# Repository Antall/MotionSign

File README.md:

View this project on [CADLAB.io](https://cadlab.io/node/895). 

# MotionSign
Controls sign activated by motion sensor.

# Setup

## Setting up Arduino and Compiling the Code (MAC)

1. Clone this repo to `~/Documents/Arduino` with `cd ~/Documents/Arduino && git clone git@github.com:bguest/MotionSign.git`
2. Change directory to MotionSign with `cd MotionSign`
3. Mod setup script `chmod +x setup.sh`
4. Run Setup `.\setup.sh` this will clone correct versions of `Adafruit_WS2801`
5. Download Arduino
6. Launch Arduino
7. Open MotionSign328
8. Set board to `Arduino HUZZAH ESP8266`
9. Set cpu frequency to `80MHz`
10. Set upload speed to `115200`
10. Verify and Upload Code

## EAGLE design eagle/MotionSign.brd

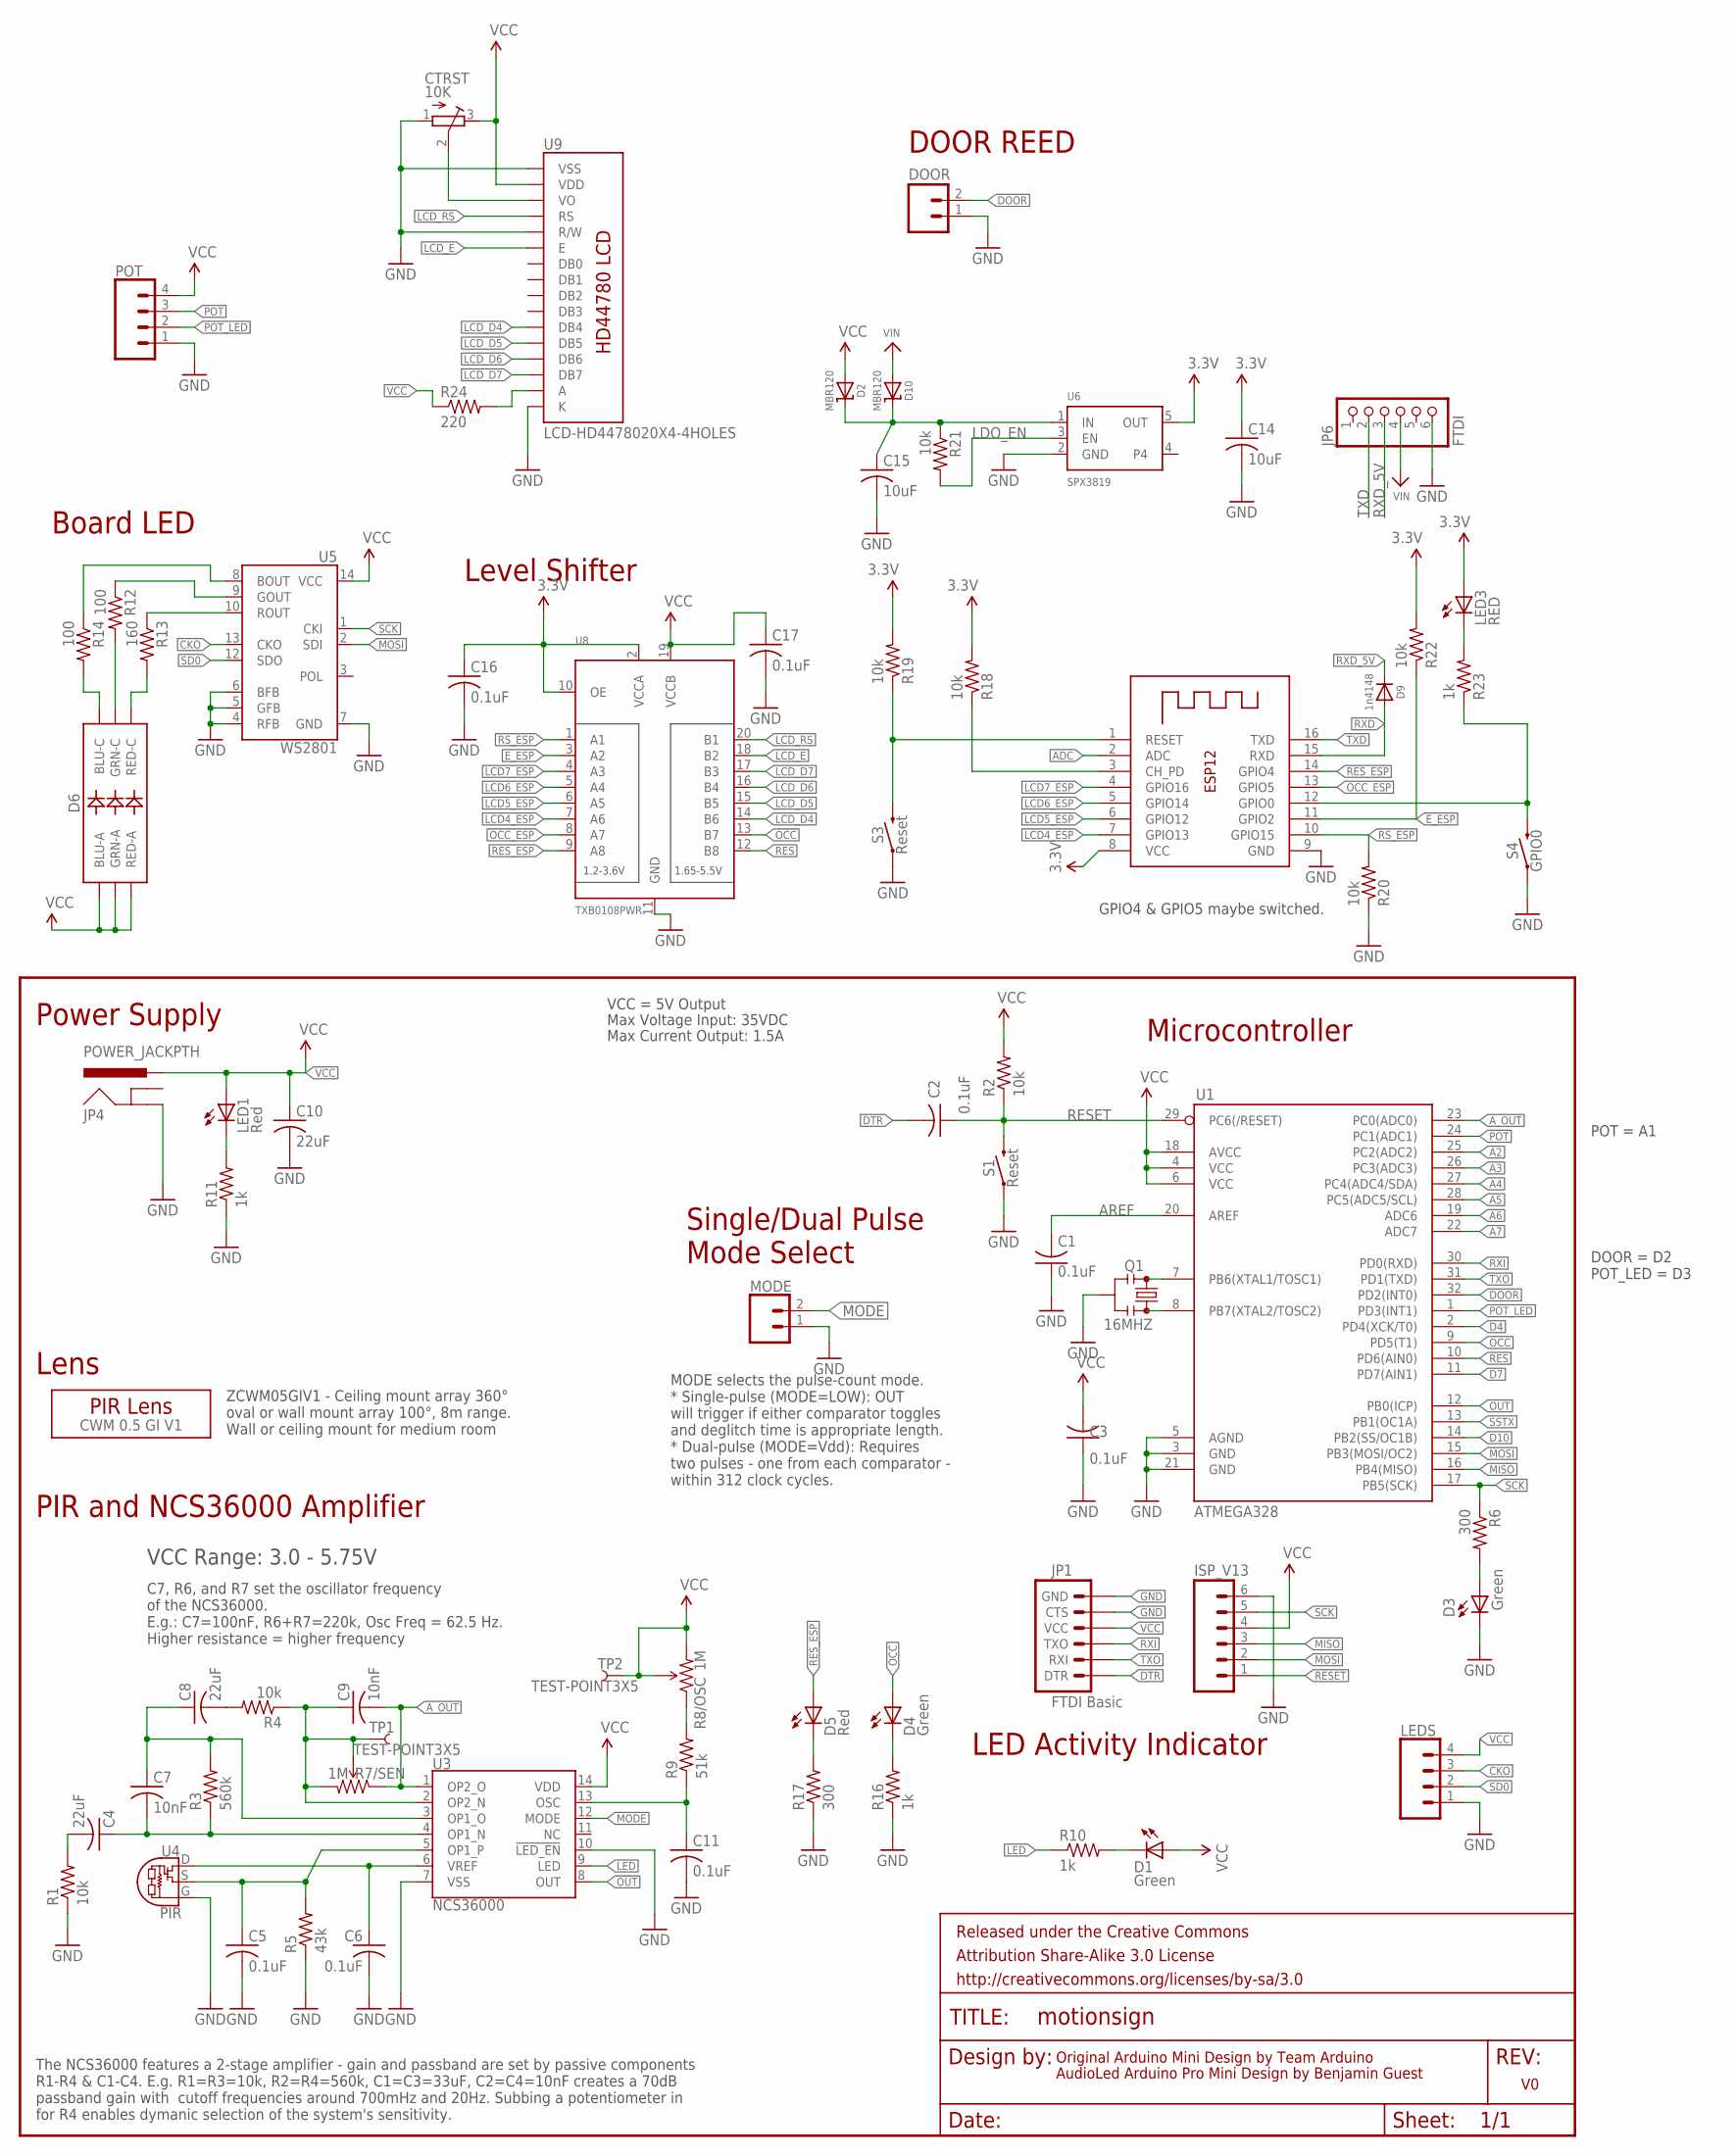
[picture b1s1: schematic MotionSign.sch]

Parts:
C1, C2, C3, C5, C6, C11, C16, C17: 0.1uF; C0805
C4, C8, C10: 22uF; C0805
C7, C9: 10nF; C0805
C14, C15: 10uF; C0805
CTRST: 10K; RTRIM3296W
D1, D3, D4: Green; CHIPLED_0805
D2, D10: MBR120; SOD-123
D5: Red; CHIPLED_0805
D6: LED-RGBNO_IC; LED-TRICOLOR-5050
D9: 1n4148; SOD-323
DOOR: CONN_02JST-PTH-2; JST-2-PTH
FRAME1: FRAME-LETTER; CREATIVE_COMMONS
ISP_V13: M06SIP; 1X06
JP1: FTDI Basic; 1X06
JP4: POWER_JACKPTH; POWER_JACK_PTH
JP6: FTDI; 1X06_ROUND_70
LED1: Red; CHIPLED_0805
LED3: RED; CHIP-LED0805
LEDS: CONN_04JST-PTH; JST-4-PTH
MODE: CONN_02; 1X02
POT: CONN_04JST-PTH; JST-4-PTH
Q1: 16MHZ; RESONATOR-SMD
R1, R2, R4, R18, R19, R20, R21, R22: 10k; M0805
R3: 560k; M0805
R5: 43k; M0805
R6, R17: 300; M0805
R7/SEN, R8/OSC: 1M; TRIMPOT-TC33X
R9: 51k; M0805
R10, R11, R16, R23: 1k; M0805
R12, R14: 100; M0805
R13: 160; M0805
R24: 220; 0204/7
S1, S3: Reset; TACTILE_SWITCH_SMD_5.2MM
S4: GPIO0; TACTILE_SWITCH_SMD_5.2MM
TP1, TP2: TEST-POINT3X5; PAD.03X.05
U1: ATMEGA328; TQFP32-08
U3: NCS36000; SO14
U4: PIR
U5: WS2801; SOP-14
U6: SPX3819; SOT23-5
U8: TXB0108PWR; TSSOP20
U9: LCD-HD4478020X4-4HOLES; LCD-20X4-1HOLE_NOSILK
U$1: CWM 0.5 GI V1; LENS-CWM-0.5-GI-V1
X2: ESP-12

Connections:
3.3V: C14.1, C16.1, LED3.A, R18.2, R19.2, R22.2, U6.5 (OUT), U8.2 (VCCA), U8.10 (OE), X2.8 (VCC)
A2: U1.25 (PC2(ADC2))
A3: U1.26 (PC3(ADC3))
A4: U1.27 (PC4(ADC4/SDA))
A5: U1.28 (PC5(ADC5/SCL))
A6: U1.19 (ADC6)
A7: U1.22 (ADC7)
ADC: X2.2 (ADC)
AREF: C1.2, U1.20 (AREF)
A_OUT: C9.2, R7/SEN.1 (CCW), U1.23 (PC0(ADC0)), U3.1 (OP2_O)
CH_PD: R18.1, X2.3 (CH_PD)
CKO: LEDS.3, U5.13 (CKO)
D4: U1.2 (PD4(XCK/T0))
D7: U1.11 (PD7(AIN1))
D10: U1.14 (PB2(SS/OC1B))
DOOR: DOOR.2, U1.32 (PD2(INT0))
DTR: C2.2, JP1.1 (DTR)
E_ESP: R22.1, U8.3 (A2), X2.11 (GPIO2)
GND: C1.1, C3.1, C5.2, C6.2, C10.2, C11.2, C14.2, C15.2, C16.2, C17.2, CTRST.1 (A), D3.C, DOOR.1, ISP_V13.6, JP1.5 (CTS), JP1.6 (GND), JP4.GND, JP6.6, LEDS.1, MODE.1, POT.1, Q1.2, R1.1, R5.1, R11.1, R16.1, R17.1, R20.1, S1.1, S1.2 (1), S3.1, S3.2 (1), S4.1, S4.2 (1), U1.3 (GND), U1.5 (AGND), U1.21 (GND), U3.7 (VSS), U3.10 (!LED_EN!), U4.G, U5.4 (RFB), U5.5 (GFB), U5.6 (BFB), U5.7 (GND), U6.2 (GND), U8.11 (GND), U9.P$1 (VSS), U9.P$5 (R/W), U9.P$16 (K), X2.9 (GND)
GPIO0: R23.1, S4.3 (2), S4.4 (2), X2.12 (GPIO0)
LCD4_ESP: U8.7 (A6), X2.7 (GPIO13)
LCD5_ESP: U8.6 (A5), X2.6 (GPIO12)
LCD6_ESP: U8.5 (A4), X2.5 (GPIO14)
LCD7_ESP: U8.4 (A3), X2.4 (GPIO16)
LCD_D4: U8.14 (B6), U9.P$11 (DB4)
LCD_D5: U8.15 (B5), U9.P$12 (DB5)
LCD_D6: U8.16 (B4), U9.P$13 (DB6)
LCD_D7: U8.17 (B3), U9.P$14 (DB7)
LCD_E: U8.18 (B2), U9.P$6 (E)
LCD_RS: U8.20 (B1), U9.P$4 (RS)
LDO_EN: R21.2, U6.3 (EN)
LED: R10.1, U3.9 (LED)
MISO: ISP_V13.3, U1.16 (PB4(MISO))
MODE: MODE.2, U3.12 (MODE)
MOSI: ISP_V13.2, U1.15 (PB3(MOSI/OC2)), U5.2 (SDI)
unnamed: Q1.3, U1.8 (PB7(XTAL2/TOSC2))
unnamed: Q1.1, U1.7 (PB6(XTAL1/TOSC1))
unnamed: C6.1, U3.6 (VREF), U4.D
unnamed: LED1.C, R11.2
unnamed: C5.1, R5.2, U3.5 (OP1_P), U4.S
unnamed: C4.2, R1.2
unnamed: D3.A, R6.2
unnamed: C8.2, R4.2
unnamed: C4.1, C7.2, R3.1, U3.4 (OP1_N)
unnamed: C7.1, C8.1, R3.2, U3.3 (OP1_O)
unnamed: C9.1, R4.1, R7/SEN.2 (WIPER), R7/SEN.3 (CW), TP1.P$1, U3.2 (OP2_N)
unnamed: C11.1, R9.1, U3.13 (OSC)
unnamed: R8/OSC.1 (CCW), R9.2
unnamed: D1.C, R10.2
unnamed: R14.1, U5.8 (BOUT)
unnamed: R13.1, U5.10 (ROUT)
unnamed: LED3.C, R23.2
unnamed: D5.C, R17.2
unnamed: R12.1, U5.9 (GOUT)
unnamed: D6.4 (BLU-C), R14.2
unnamed: D6.6 (GRN-C), R12.2
unnamed: D6.5 (RED-C), R13.2
unnamed: C15.1, D2.C, D10.C, R21.1, U6.1 (IN)
unnamed: D4.C, R16.2
unnamed: R24.2, U9.P$15 (A)
OCC: D4.A, U1.9 (PD5(T1)), U8.13 (B7)
OCC_ESP: U8.8 (A7), X2.13 (GPIO5)
OUT: U1.12 (PB0(ICP)), U3.8 (OUT)
POT: POT.3, U1.24 (PC1(ADC1))
POT_LED: POT.2, U1.1 (PD3(INT1))
RES: U1.10 (PD6(AIN0)), U8.12 (B8)
RESET: C2.1, ISP_V13.1, R2.1, S1.3 (2), S1.4 (2), U1.29 (PC6(/RESET))
RESET_HZA: R19.1, S3.3 (2), S3.4 (2), X2.1 (RESET)
RES_ESP: D5.A, U8.9 (A8), X2.14 (GPIO4)
RS_ESP: R20.2, U8.1 (A1), X2.10 (GPIO15)
RXD: D9.A, X2.15 (RXD)
RXD_5V: D9.C, JP6.3
RXI: JP1.3 (TXO), U1.30 (PD0(RXD))
SCK: ISP_V13.5, R6.1, U1.17 (PB5(SCK)), U5.1 (CKI)
SD0: LEDS.2, U5.12 (SDO)
SSTX: U1.13 (PB1(OC1A))
TXD: JP6.2, X2.16 (TXD)
TXO: JP1.2 (RXI), U1.31 (PD1(TXD))
VCC: C3.2, C10.1, C17.1, CTRST.3 (E), D1.A, D2.A, D6.1 (GRN-A), D6.2 (RED-A), D6.3 (BLU-A), ISP_V13.4, JP1.4 (VCC), JP4.PWR, LED1.A, LEDS.4, POT.4, R2.2, R8/OSC.2 (WIPER), R8/OSC.3 (CW), R24.1, TP2.P$1, U1.4 (VCC), U1.6 (VCC), U1.18 (AVCC), U3.14 (VDD), U5.14 (VCC), U8.19 (VCCB), U9.P$2 (VDD)
VIN: D10.A, JP6.4
VO: CTRST.2 (S), U9.P$3 (VO)

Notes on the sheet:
Original Arduino Mini Design by Team Arduino
AudioLed Arduino Pro Mini Design by Benjamin Guest
Max Voltage Input: 35VDC
Max Current Output: 1.5A
VCC = 5V Output
VCC Range: 3.0 - 5.75V
The NCS36000 features a 2-stage amplifier - gain and passband are set by passive components R1-R4 & C1-C4. E.g. R1=R3=10k, R2=R4=560k, C1=C3=33uF, C2=C4=10nF creates a 70dB passband gain with cutoff frequencies around 700mHz and 20Hz. Subbing a potentiometer in for R4 enables dymanic selection of t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
C7, R6, and R7 set the oscillator frequency of the NCS36000. E.g.: C7=100nF, R6+R7=220k, Osc Freq = 62.5 Hz. Higher resistance = higher frequency
PIR and NCS36000 Amplifier
ZCWM05GIV1 - Ceiling mount array 360° oval or wall mount array 100°, 8m range. Wall or ceiling mount for medium room
Lens
MODE selects the pulse-count mode. * Single-pulse (MODE=LOW): OUT will trigger if either comparator toggles and deglitch time is appropriate length. * Dual-pulse (MODE=Vdd): Requires two pulses - one from each comparator - within 312 clock cycles.
Single/Dual Pulse Mode Select
LED Activity Indicator
Power Supply
Microcontroller
Board LED
Level Shifter
GPIO4 & GPIO5 maybe switched.
DOOR REED
DOOR = D2 POT_LED = D3
POT = A1

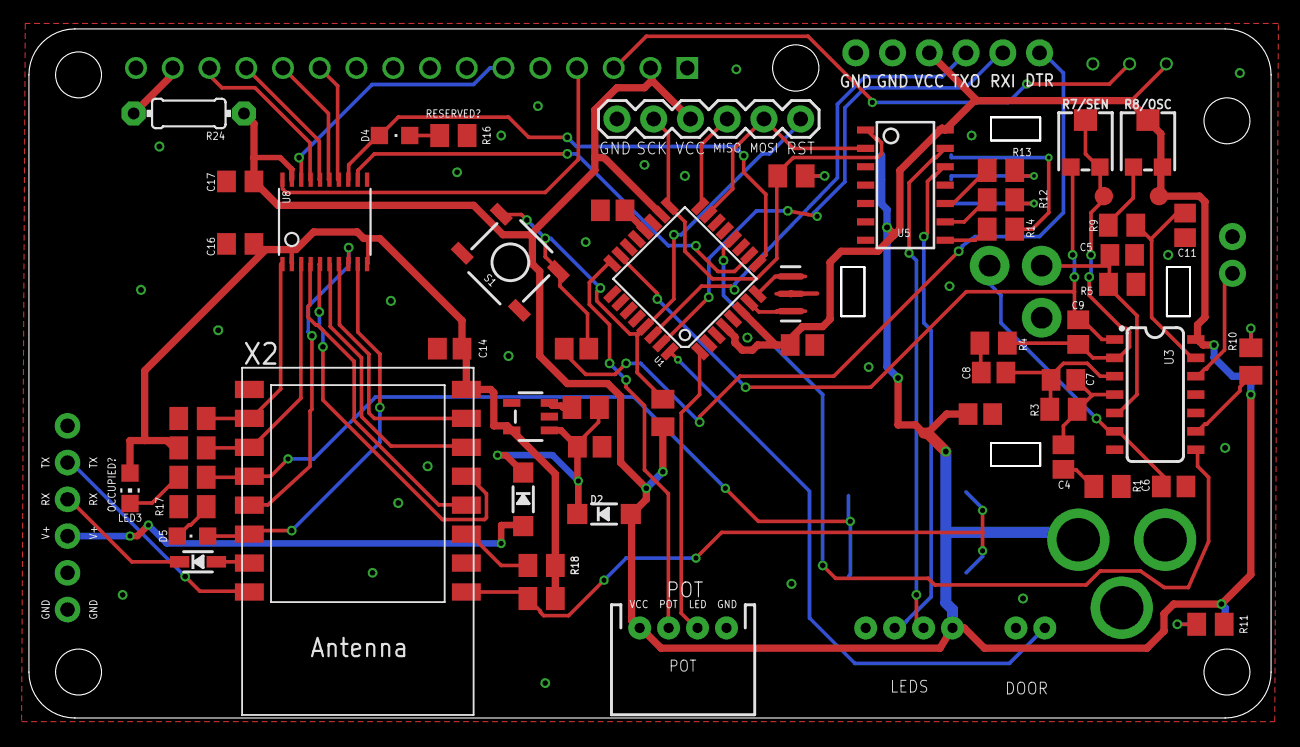
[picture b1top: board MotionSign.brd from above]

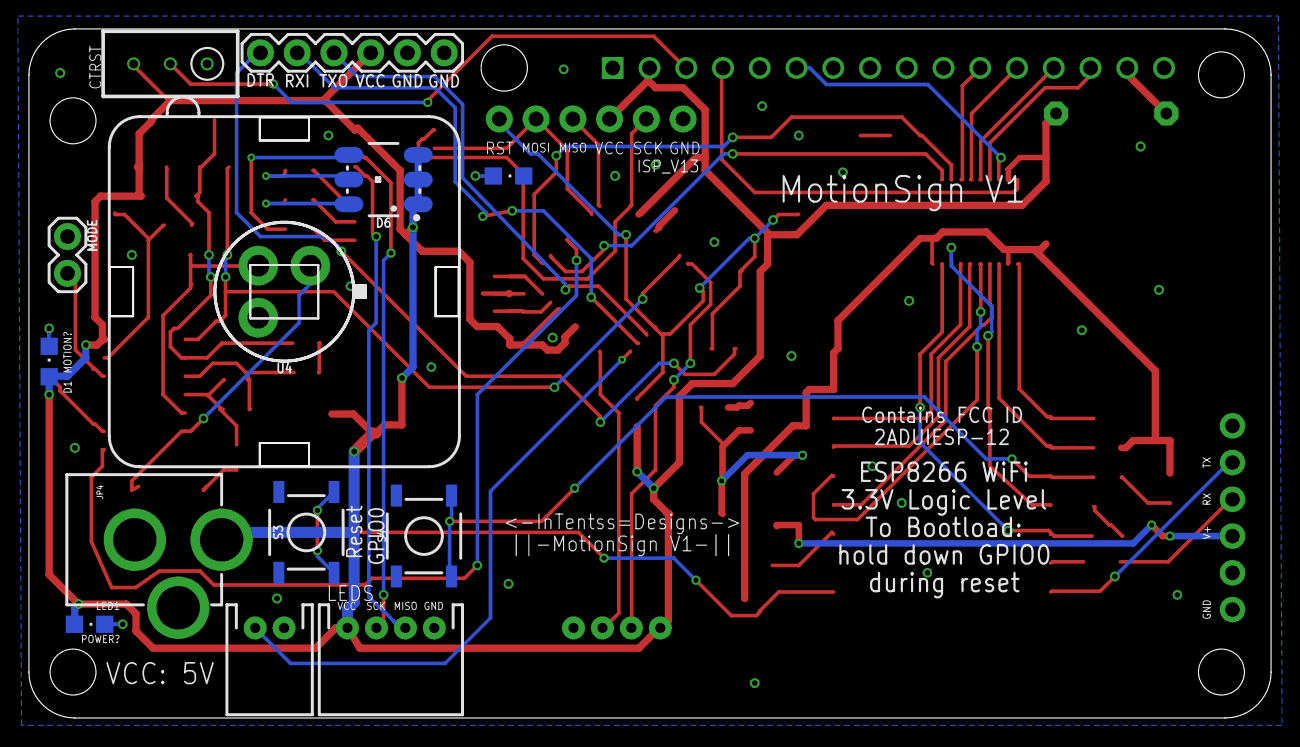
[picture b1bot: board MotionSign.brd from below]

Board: 2 copper layers, 85.7 x 47.5 mm, 73 parts (15 on the bottom side), 70 nets.

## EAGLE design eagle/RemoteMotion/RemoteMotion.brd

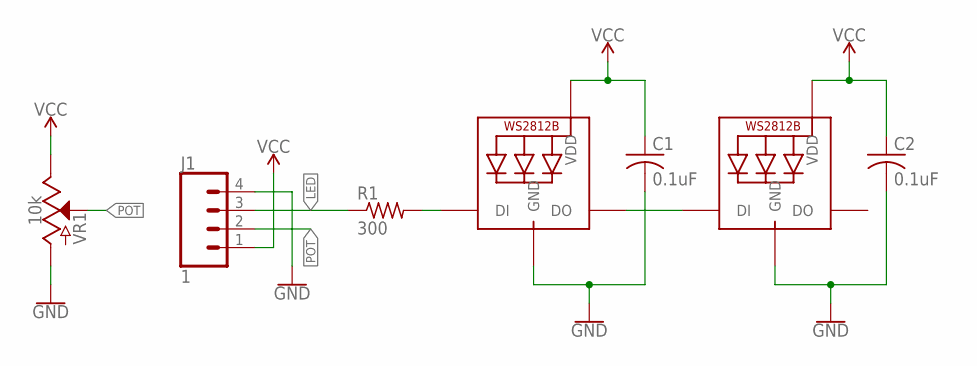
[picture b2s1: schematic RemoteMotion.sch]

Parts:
C1, C2: 0.1uF; C0805
J1: 1; JST-4-PTH
LED1, LED2: WS2812B5050; WS2812B
R1: 300; R0805
VR1: 10k; SLIDER-XLARGE

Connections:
GND: C1.2, C2.2, J1.4, LED1.3-GND (GND), LED2.3-GND (GND), VR1.3 (A)
LED: J1.3, R1.1
unnamed: LED1.4-DIN (DI), R1.2
unnamed: LED1.2-DOUT (DO), LED2.4-DIN (DI)
POT: J1.2, VR1.2A (S)
VCC: C1.1, C2.1, J1.1, LED1.1-VDD (VDD), LED2.1-VDD (VDD), VR1.1 (E)

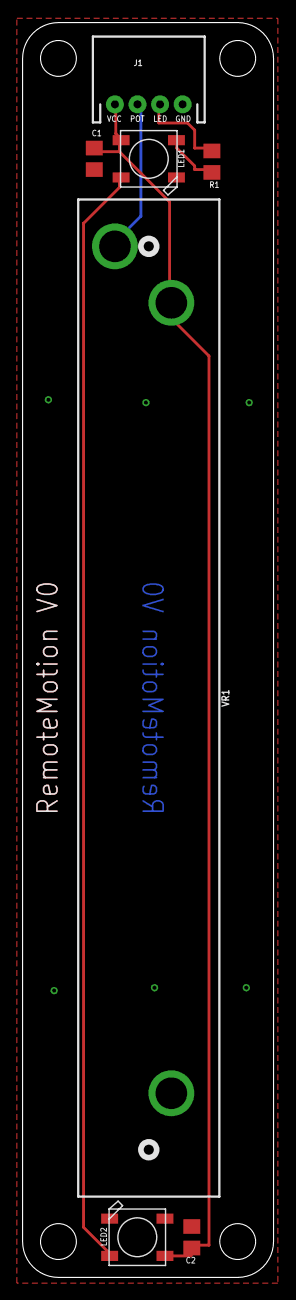
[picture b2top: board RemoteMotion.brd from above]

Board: 2 copper layers, 22.2 x 111.1 mm, 7 parts (0 on the bottom side), 6 nets.

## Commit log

2018-03-20 Add Motion, Accumulator, RangeU16
2018-03-21 Add Blue Point to Acumulator
2018-03-21 Fix Acumulator
2018-03-25 Add Eagle
2018-03-25 Move Files Around
2018-03-30 Moves and Shakes
2018-04-02 Inital setup for API
2018-04-03 Add Indicator
2018-04-12 Add Remote Motion / Work on Dispaly
2018-04-13 Add Display / Add Indicator LEDs
2018-04-13 Screen is plugged in but doesnt work
2018-04-16 Display now working, removed debug prints
2018-04-17 Work on Board
2018-04-18 V0 of board
2018-04-18 Slight board improvemnents
2018-04-18 Backlink to CADLAB.io has been added.
2018-04-25 Move to managed libarary for 3d parts
2018-04-26 More 3D parts
2018-05-02 Move labels around vias
2018-05-09 POT Cable Labels Were Backwards
2018-05-10 Set Pot led count to 2
2018-05-10 Fix board issues
2018-05-12 Switch GPIO4/GPIO5 pins
2018-05-16 Add 5V jumper
2018-05-17 Switch to Managed Libary for MotionSign
2018-05-22 Updates to Motion sign + FTDI_Extender
2018-05-23 Additions to FTDI_Extender
2018-06-12 Swap out power managment resistor with 204/7 for
    Allow for further experimentation with power managment
2018-06-13 Try to get it working better...
2018-06-14 Initial code for microservice
2018-06-15 bug fixes
2018-06-15 Add Sensitivity/Ossilation Names
2018-06-17 Add necessary endpoints
2018-06-19 Get working with secure connection / lambda endpoints
2018-06-19 switch to 60s per request remove post occupied
2018-06-19 Update to remove need for occupied post
2018-06-20 Print Mac Address
2018-06-22 Update sinatra app to match aws lambda
2018-07-01 - Interact with Google Calendar API - Add SAM for local testing
2018-07-01 Disable cache warning
2018-07-09 Fix message formatting
2018-07-11 Add delay up to 8sec for long running requests
2018-07-11 Fix formating issue
2018-07-11 Update readme and git ignore cred files
2018-07-11 Another Readme edit
2018-07-13 Reserved flag set based on google calendar, introduce Google Creds Manager
2018-07-15 Moved code around, cleant up _reserved_ method
2018-07-19 Make motion sensor more sensitive
2018-07-24 Tweaks
2018-07-26 Updates to readme
2019-02-26 Add door reed switch

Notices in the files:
parts and their libraries:
MotionSign: Released under the Creative Commons Attribution Share-Alike 3.0 License
MotionSign: http://creativecommons.org/licenses/by-sa/3.0
MotionSign: Released under the Creative Commons
